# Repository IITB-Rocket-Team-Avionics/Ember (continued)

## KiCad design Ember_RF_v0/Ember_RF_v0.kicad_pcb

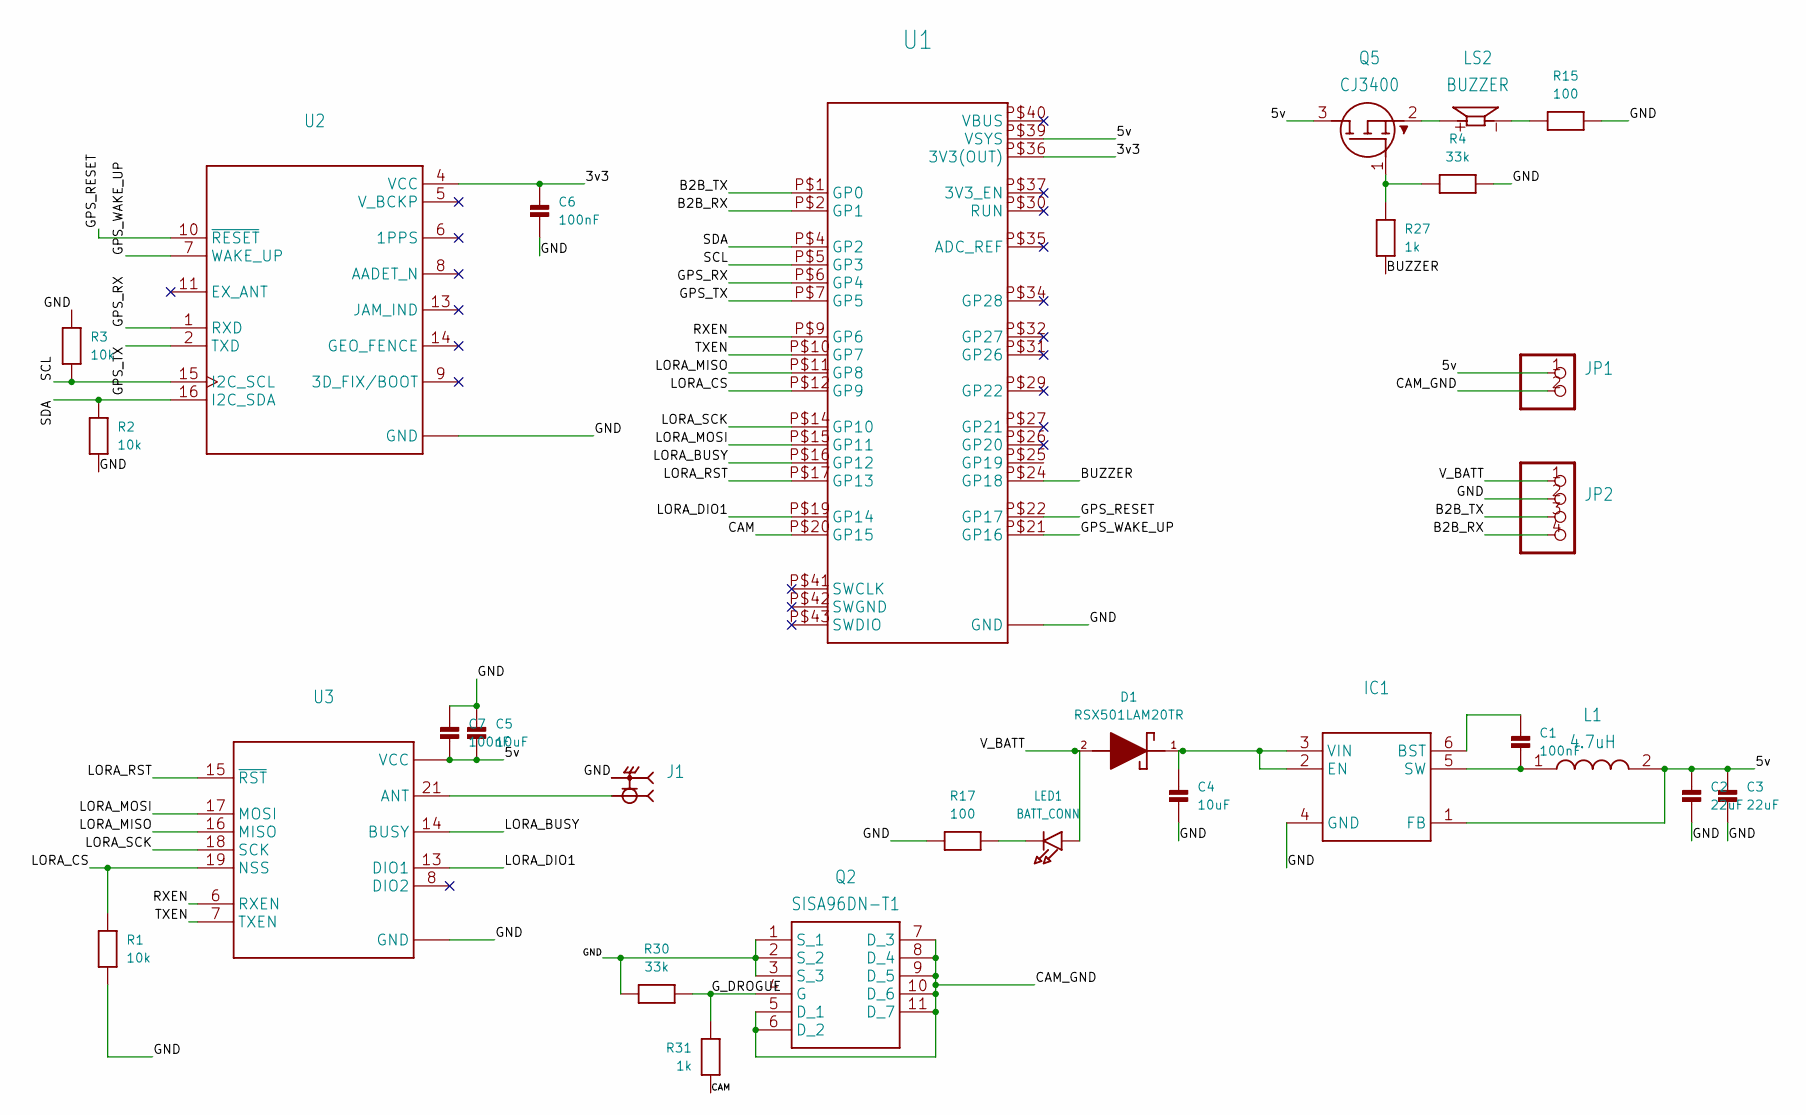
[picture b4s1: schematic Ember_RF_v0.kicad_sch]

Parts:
C1, C6, C7: 100nF; 0603
C2, C3: 22uF; 0603
C4, C5: 10uF; 0603
D1: RSX501LAM20TR; DIOM4725X105N; MOUSER_PART_NUMBER 755-RSX501LAM20TR; DigiKey_Part_Number RSX501LAM20CT-ND
IC1: SOT95P280X100-6N
J1: RFSOLUTIONS_CON-SMA-EDGE-S
JP1: 1X02_OVAL
JP2: 1X04_OVAL
L1: 4.7uH; INDPM3027X150N
LED1: BATT_CONN; CHIPLED_0603
LS2: BUZZER; CUI_CMT-8530S-SMT
Q2: SISA96DN-T1; SIS862DNT1GE3
Q5: CJ3400; SOT95P240X115-3N
R1, R2, R3: 10k; 0603
R4, R30: 33k; 0603
R15, R17: 100; 0603
R27, R31: 1k; 0603
U1: PICO-PKG-SMD
U2: XCVR_L89
U3: XCVR_E22-900M30S

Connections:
/3v3: C6.1, U1.P$36 (3V3(OUT)), U2.4 (VCC)
/5v: C2.1, C3.1, C5.2, C7.2, IC1.1 (FB), JP1.1, L1.2, Q5.3 (D), U1.P$39 (VSYS), U3.9 (VCC), U3.10 (VCC)
/B2B_RX: JP2.4, U1.P$2 (GP1)
/B2B_TX: JP2.3, U1.P$1 (GP0)
/BUZZER: R27.1, U1.P$24 (GP18)
/CAM: R31.1, U1.P$20 (GP15)
/CAM_GND: JP1.2, Q2.5 (D_1), Q2.6 (D_2), Q2.7 (D_3), Q2.8 (D_4), Q2.9 (D_5), Q2.10 (D_6), Q2.11 (D_7)
/GND: C2.2, C3.2, C4.2, C5.1, C6.2, C7.1, IC1.4 (GND), J1.G1 (2), J1.G2 (2), J1.G3 (2), J1.G4 (2), JP2.2, Q2.1 (S_1), Q2.2 (S_2), Q2.3 (S_3), R1.1, R2.1, R3.2, R4.2, R15.2, R17.1, R30.2, U1.P$3 (GND), U1.P$8 (GND), U1.P$13 (GND), U1.P$18 (GND), U1.P$23 (GND), U1.P$28 (GND), U1.P$33 (GND), U1.P$38 (GND), U2.3 (GND), U2.12 (GND), U3.1 (GND), U3.2 (GND), U3.3 (GND), U3.4 (GND), U3.5 (GND), U3.11 (GND), U3.12 (GND), U3.20 (GND), U3.22 (GND)
/GPS_RESET: U1.P$22 (GP17), U2.10 (~RESET)
/GPS_RX: U1.P$6 (GP4), U2.1 (RXD)
/GPS_TX: U1.P$7 (GP5), U2.2 (TXD)
/GPS_WAKE_UP: U1.P$21 (GP16), U2.7 (WAKE_UP)
/G_DROGUE: Q2.4 (G), R30.1, R31.2
/LORA_BUSY: U1.P$16 (GP12), U3.14 (BUSY)
/LORA_CS: R1.2, U1.P$12 (GP9), U3.19 (NSS)
/LORA_DIO1: U1.P$19 (GP14), U3.13 (DIO1)
/LORA_MISO: U1.P$11 (GP8), U3.16 (MISO)
/LORA_MOSI: U1.P$15 (GP11), U3.17 (MOSI)
/LORA_RST: U1.P$17 (GP13), U3.15 (~RST)
/LORA_SCK: U1.P$14 (GP10), U3.18 (SCK)
/RXEN: U1.P$9 (GP6), U3.6 (RXEN)
/SCL: R3.1, U1.P$5 (GP3), U2.15 (I2C_SCL)
/SDA: R2.2, U1.P$4 (GP2), U2.16 (I2C_SDA)
/TXEN: U1.P$10 (GP7), U3.7 (TXEN)
/V_BATT: D1.2, JP2.1, LED1.A
unnamed: C1.1, IC1.6 (BST)
unnamed: C1.2, IC1.5 (SW), L1.1
unnamed: C4.1, D1.1, IC1.2 (EN), IC1.3 (VIN)
unnamed: LED1.C, R17.2
unnamed: LS2.N, R15.1
unnamed: Q5.1 (G), R4.1, R27.2
unnamed: LS2.P, Q5.2 (S)
unnamed: J1.1, U3.21 (ANT)

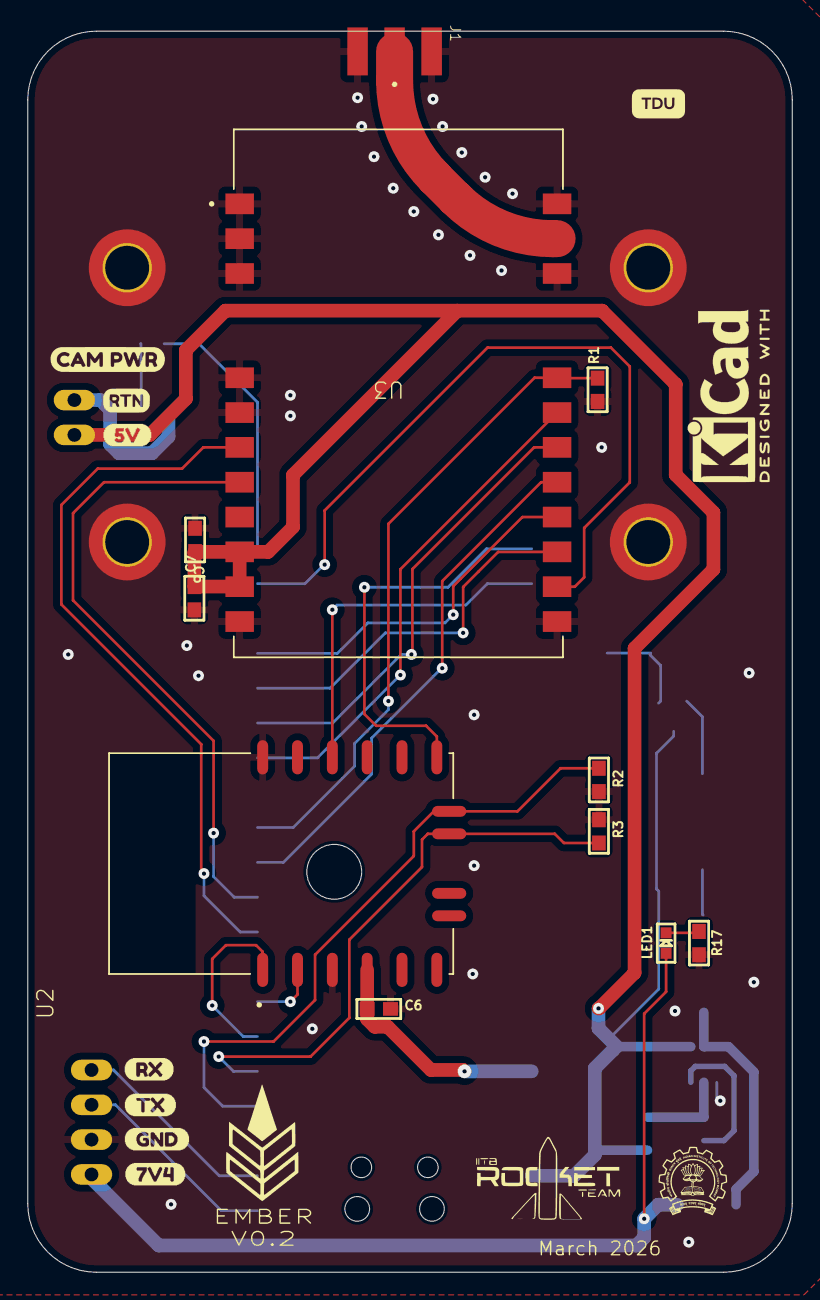
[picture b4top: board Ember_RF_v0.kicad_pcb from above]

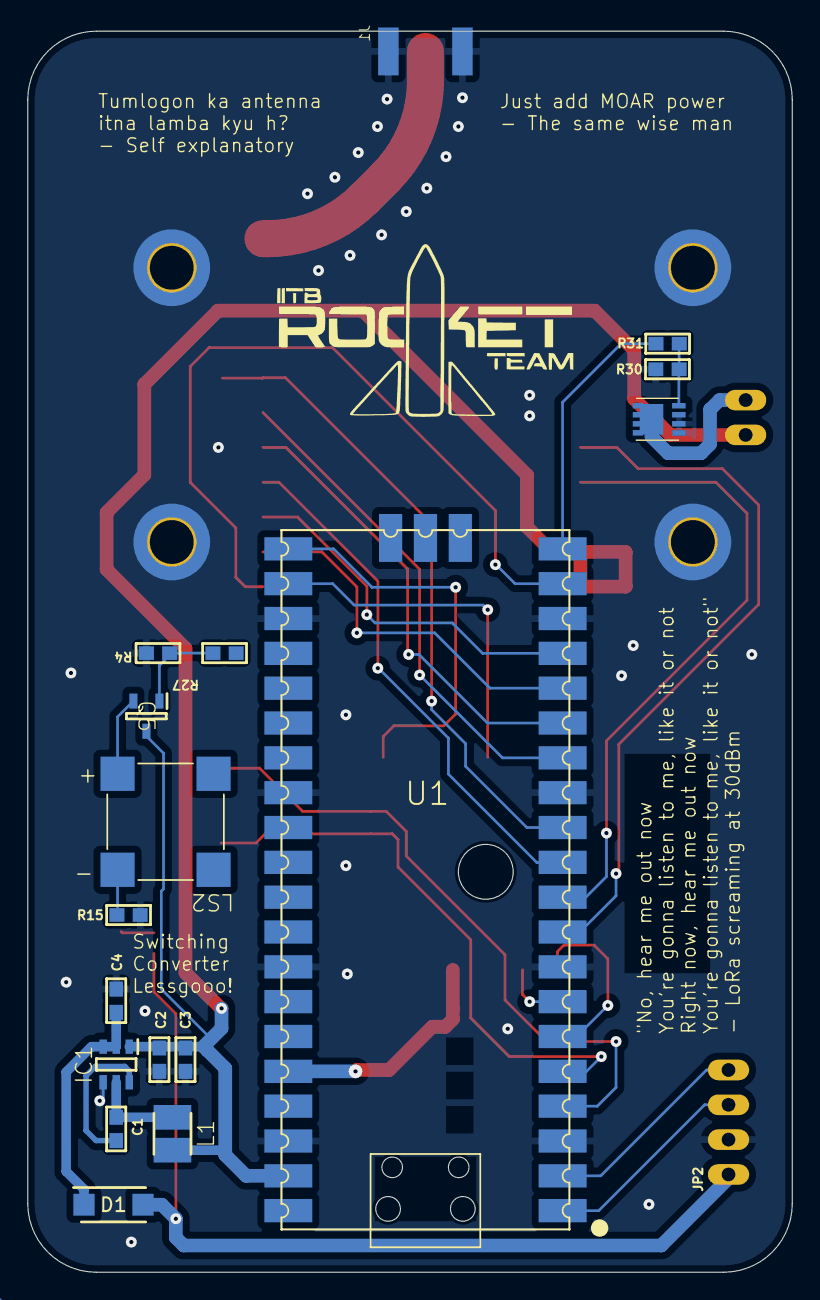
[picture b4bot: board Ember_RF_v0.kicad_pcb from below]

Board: 2 copper layers, 55.8 x 90.5 mm, 29 parts (18 on the bottom side), 33 nets.

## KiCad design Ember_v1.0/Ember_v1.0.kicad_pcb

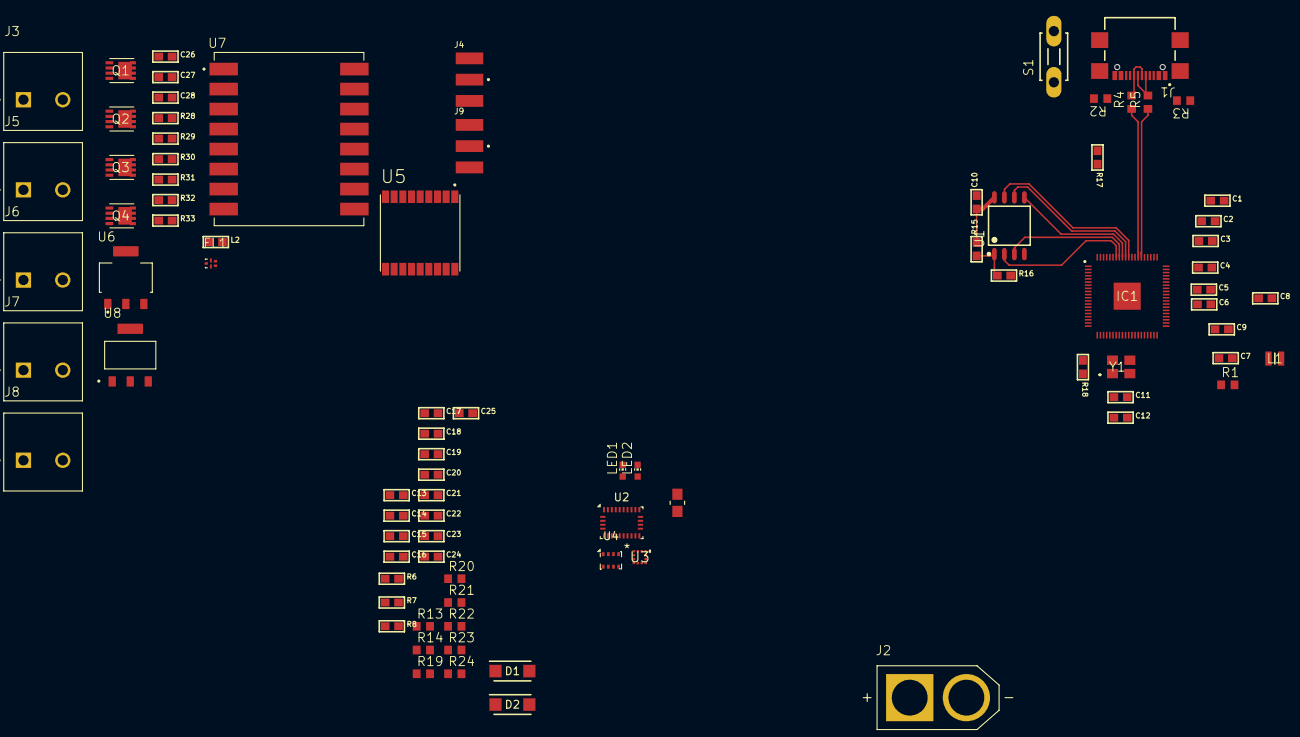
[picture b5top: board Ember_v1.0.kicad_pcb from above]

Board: 4 copper layers, 86 parts (0 on the bottom side), 55 nets.

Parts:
C1, C2, C3, C4, C6, C10, C13, C16: 100 nF; 0603
C5: 1 uF; 0603
C7, C8, C9: 4.7 uF; 0603
C11, C12: 18pF; 0603
C14, C15, C21: 10 uF; 0603
C17, C18, C19, C26, C27, C28: 0603
C20, C22, C23: 120 pF; 0603
C24, C25: 20 pF; 0603
D1, D2: RSX501LAM20TR; DIOM4725X105N
FL1: Saw_filter; FIL_AFS14A04-1575.42-T3
IC1: QFN40P1000X1000X90-81N
J1: USB_C; GCT_USB4110GFA
J2: BATT_CONN; AMASS_XT60-M
J3: DROGUE; ONSHORE_OSTTA020161
J4, J9: RFSOLUTIONS_CON-SMA-EDGE-S
J5: MAIN; ONSHORE_OSTTA020161
J6: MAN2; ONSHORE_OSTTA020161
J7: DROGUE2; ONSHORE_OSTTA020161
J8: ARM; ONSHORE_OSTTA020161
L1: 3.3 uH; LQM2MPN1R0NG0L
L2: 0603
LED1: V_BATT; CHIP-LED0603
LED2: VBUS; CHIP-LED0603
Q1, Q2, Q3, Q4: SISA96DN-T1; SIS862DNT1GE3
R1: R0603
R2, R3: 5.1k; R0603
R4, R5: 27.4; R0603
R6, R28, R30, R32: 33k; 0603
R7, R18, R29, R31, R33: 1k; 0603
R8: 4.7k; 0603
R13, R14: 100; R0603
R15: 10 kohm; 0603
R16: 0 ohm; 0603
R17: 0603
R19, R20, R21, R22, R23, R24: 10 kohm; R0603
S1: DTS-3
U1: FLASH_128K; SOIC127P790X216-8N
U2: BNO055; LGA-28_5.2x3.8mm_P0.5mm
U3: LGA12_2X2X0P9_ROM
U4: BMP280; Bosch_LGA-8_2x2.5mm_P0.65mm_ClockwisePinNumbering
U5: Teseo_liv3f; TESEO-LIV3F
U6, U8: SOT229P700X180-4N
U7: Waveshare_SX1262; XCVR_CORE1262-868M
XTAL1: XTAL_FC135; XTAL_FC-135_EPS
Y1: YSX321SL

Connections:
/Main_board/1v1: C5.1, C6.1, C8.1, IC1.10 (DVDD_1), IC1.32 (DVDD_2), IC1.51 (DVDD_3), IC1.65 (VREG_FB), L1.2
/Main_board/3v3: C1.1, C2.1, C3.1, C4.1, C9.1, C10.1, C13.2, C14.1, C15.1, C17.1, C18.1, IC1.5 (IOVDD_1), IC1.15 (IOVDD_2), IC1.24 (IOVDD_3), IC1.29 (IOVDD_4), IC1.35 (RUN), IC1.41 (IOVDD_5), IC1.50 (IOVDD_6), IC1.59 (ADC_AVDD), IC1.60 (IOVDD_7), IC1.64 (VREG_VIN), IC1.68 (USB_OTP_VDD), IC1.69 (QSPI_IOVDD), IC1.76 (IOVDD_8), R1.2, R15.2, R20.1, R21.1, R22.1, R24.1, U1.8 (VCC), U2.3 (VDD), U2.4 (~BOOT_LOAD_PIN), U2.28 (VDDIO), U3.1 (SDO/ADDR), U3.3 (IO_VDD), U3.7 (VDD), U3.10 (NCS), U4.6 (VDDIO), U4.8 (VDD), U6.2 (VOUT), U6.4 (VOUT)
/Main_board/5v: C26.1, C27.1, D1.2, LED1.A, U8.2 (VOUT)
/Main_board/D_N: IC1.66 (USB_DM), R5.1
/Main_board/D_Nr: J1.A7 (DN1), J1.B7 (DN2), R5.2
/Main_board/D_P: IC1.67 (USB_DP), R4.1
/Main_board/D_Pr: J1.A6 (DP1), J1.B6 (DP2), R4.2
/Main_board/FLASH_EXT_CS: IC1.77 (GPIO0), R16.2
/Main_board/GND: C1.2, C2.2, C3.2, C4.2, C5.2, C6.2, C7.2, C8.2, C9.2, C10.2, C11.2, C12.1, C13.1, C14.2, C15.2, C16.1, C17.2, C18.2, C19.2, C24.1, C25.1, C26.2, C27.2, C28.2, IC1.62 (VREG_PGND), IC1.81 (GND), J1.A1/B12 (GND), J1.B1/A12 (GND), J1.S1 (GND), J1.S2 (GND), J1.S3 (GND), J1.S4 (GND), J2.N (NEG), Q1.1 (S_1), Q1.2 (S_2), Q1.3 (S_3), Q2.1 (S_1), Q2.2 (S_2), Q2.3 (S_3), Q3.1 (S_1), Q3.2 (S_2), Q3.3 (S_3), Q4.1 (S_1), Q4.2 (S_2), Q4.3 (S_3), R2.2, R3.1, R6.2, R14.2, R19.1, R23.1, R28.2, R30.2, R32.2, S1.2, U1.4 (GND), U2.2 (GND), U2.5 (PS1), U2.6 (PS0), U2.18 (COM2), U2.25 (GNDIO), U3.4 (TRIG), U3.8 (GND_2), U3.9 (GND), U4.1 (GND), U4.7 (GND), U6.1 (ADJ/GND), U8.1 (GND/ADJ), Y1.2 (GND_1), Y1.4 (GND_2)
/Main_board/G_DROGUE: Q2.4 (G), R30.1, R31.2
/Main_board/G_MAIN: Q3.4 (G), R32.1, R33.2
/Main_board/G_MAIN2: Q1.4 (G), R28.1, R29.2
/Main_board/PYRO_DROGUE: J3.2, Q2.5 (D_1), Q2.6 (D_2), Q2.7 (D_3), Q2.8 (D_4), Q2.9 (D_5), Q2.10 (D_6), Q2.11 (D_7)
/Main_board/PYRO_DROGUE2: J7.2, Q4.5 (D_1), Q4.6 (D_2), Q4.7 (D_3), Q4.8 (D_4), Q4.9 (D_5), Q4.10 (D_6), Q4.11 (D_7)
/Main_board/PYRO_MAIN: J5.2, Q3.5 (D_1), Q3.6 (D_2), Q3.7 (D_3), Q3.8 (D_4), Q3.9 (D_5), Q3.10 (D_6), Q3.11 (D_7)
/Main_board/PYRO_MAIN2: J6.2, Q1.5 (D_1), Q1.6 (D_2), Q1.7 (D_3), Q1.8 (D_4), Q1.9 (D_5), Q1.10 (D_6), Q1.11 (D_7)
/Main_board/QSPI_SCLK: IC1.71 (QSPI_SCLK), U1.6 (CLK)
/Main_board/QSPI_SD0: IC1.72 (QSPI_SD0), U1.5 (DI(IO0))
/Main_board/QSPI_SD1: IC1.74 (QSPI_SD1), U1.2 (DO(IO1))
/Main_board/QSPI_SD2: IC1.73 (QSPI_SD2), U1.3 (~WP(IO2))
/Main_board/QSPI_SD3: IC1.70 (QSPI_SD3), U1.7 (~HOLD/~RESET(IO3))
/Main_board/QSPI_SS: IC1.75 (QSPI_SS), R17.2
/Main_board/SCL: IC1.2 (GPIO5), R21.2, U2.19 (COM1), U3.12 (SCLK/SCL), U4.4 (SCK)
/Main_board/SDA: IC1.1 (GPIO4), R20.2, U2.20 (COM0), U3.2 (SDI/SDA), U4.3 (SDI)
/Main_board/VBUS: D2.2, J1.A4/B9 (VBUS), J1.B4/A9 (VBUS), LED2.A
/Main_board/VCC_PYRO: J3.1, J5.1, J6.1, J7.1, J8.1
/Main_board/V_BATT: C28.1, J2.P (POS), J8.2, U8.3 (VIN)
/Main_board/V_MUX_OUT: C19.1, D1.1, D2.1, U6.3 (VIN)
/Main_board/XIN: C12.2, IC1.30 (XIN), Y1.3 (CRYSTAL_2)
/Main_board/XIN32: C24.2, U2.27 (XIN32), XTAL1.1
/Main_board/XOUT: IC1.31 (XOUT), R18.1
/Main_board/XOUT32: C25.2, U2.26 (XOUT32), XTAL1.2
/RF_board/3v3: C21.2, U5.6 (VBATT), U5.7 (VCC_IO), U5.8 (VCC), U7.8 (3V3)
/RF_board/GND: C21.1, C23.1, FL1.B (GND), FL1.D (GND), FL1.E (GND), J4.G1 (2), J4.G2 (2), J4.G3 (2), J4.G4 (2), J9.G1 (2), J9.G2 (2), J9.G3 (2), J9.G4 (2), R8.1, U5.1 (GND), U5.10 (GND_RF), U5.12 (GND_RF), U7.1 (GND), U7.2 (GND), U7.7 (GND), U7.15 (GND)
/RF_board/GPS_ANT: C22.1, C23.2, J4.1, L2.2
/RF_board/GPS_RF_IN: C20.2, U5.11 (RF_IN)
/RF_board/LORA_CS: R8.2, U7.14 (CS)
/RF_board/LoRa_ANT: J9.1, U7.16 (ANT)
/RF_board/SAW_IN: C22.2, FL1.C (IN)
/RF_board/SAW_OUT: C20.1, FL1.A (OUT)
unnamed: C7.1, IC1.61 (VREG_AVDD), R1.1
unnamed: C11.1, R18.2, Y1.1 (CRYSTAL_1)
unnamed: C16.2, U2.9 (CAP)
unnamed: IC1.63 (VREG_LX), L1.1
unnamed: J1.A5 (CC1), R3.2
unnamed: J1.B5 (CC2), R2.1
unnamed: LED1.C, R14.1
unnamed: LED2.C, R13.1
unnamed: Q4.4 (G), R6.1, R7.2
unnamed: R17.1, S1.1
unnamed: R15.1, R16.1, U1.1 (~CS)
unnamed: R23.2, U2.17 (COM3)
unnamed: R22.2, U2.11 (~RESET)
unnamed: R24.2, U4.2 (CSB)
unnamed: R19.2, U4.5 (SDO)

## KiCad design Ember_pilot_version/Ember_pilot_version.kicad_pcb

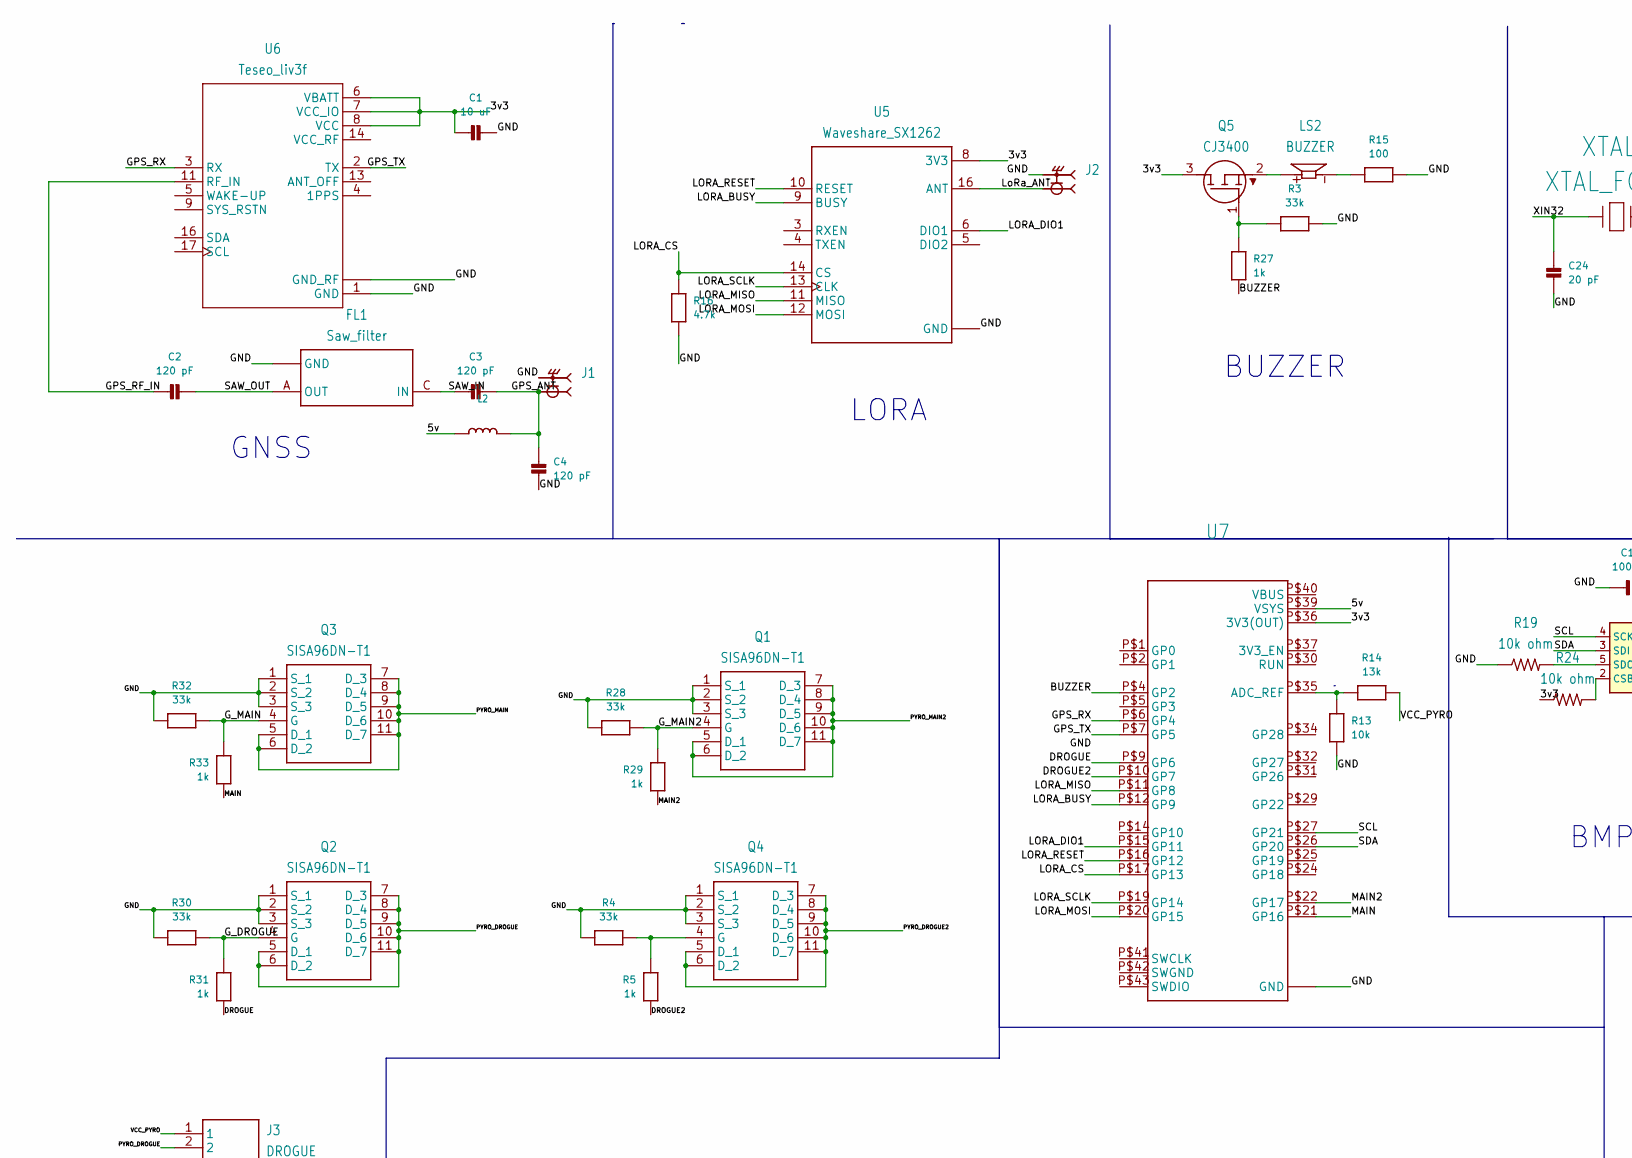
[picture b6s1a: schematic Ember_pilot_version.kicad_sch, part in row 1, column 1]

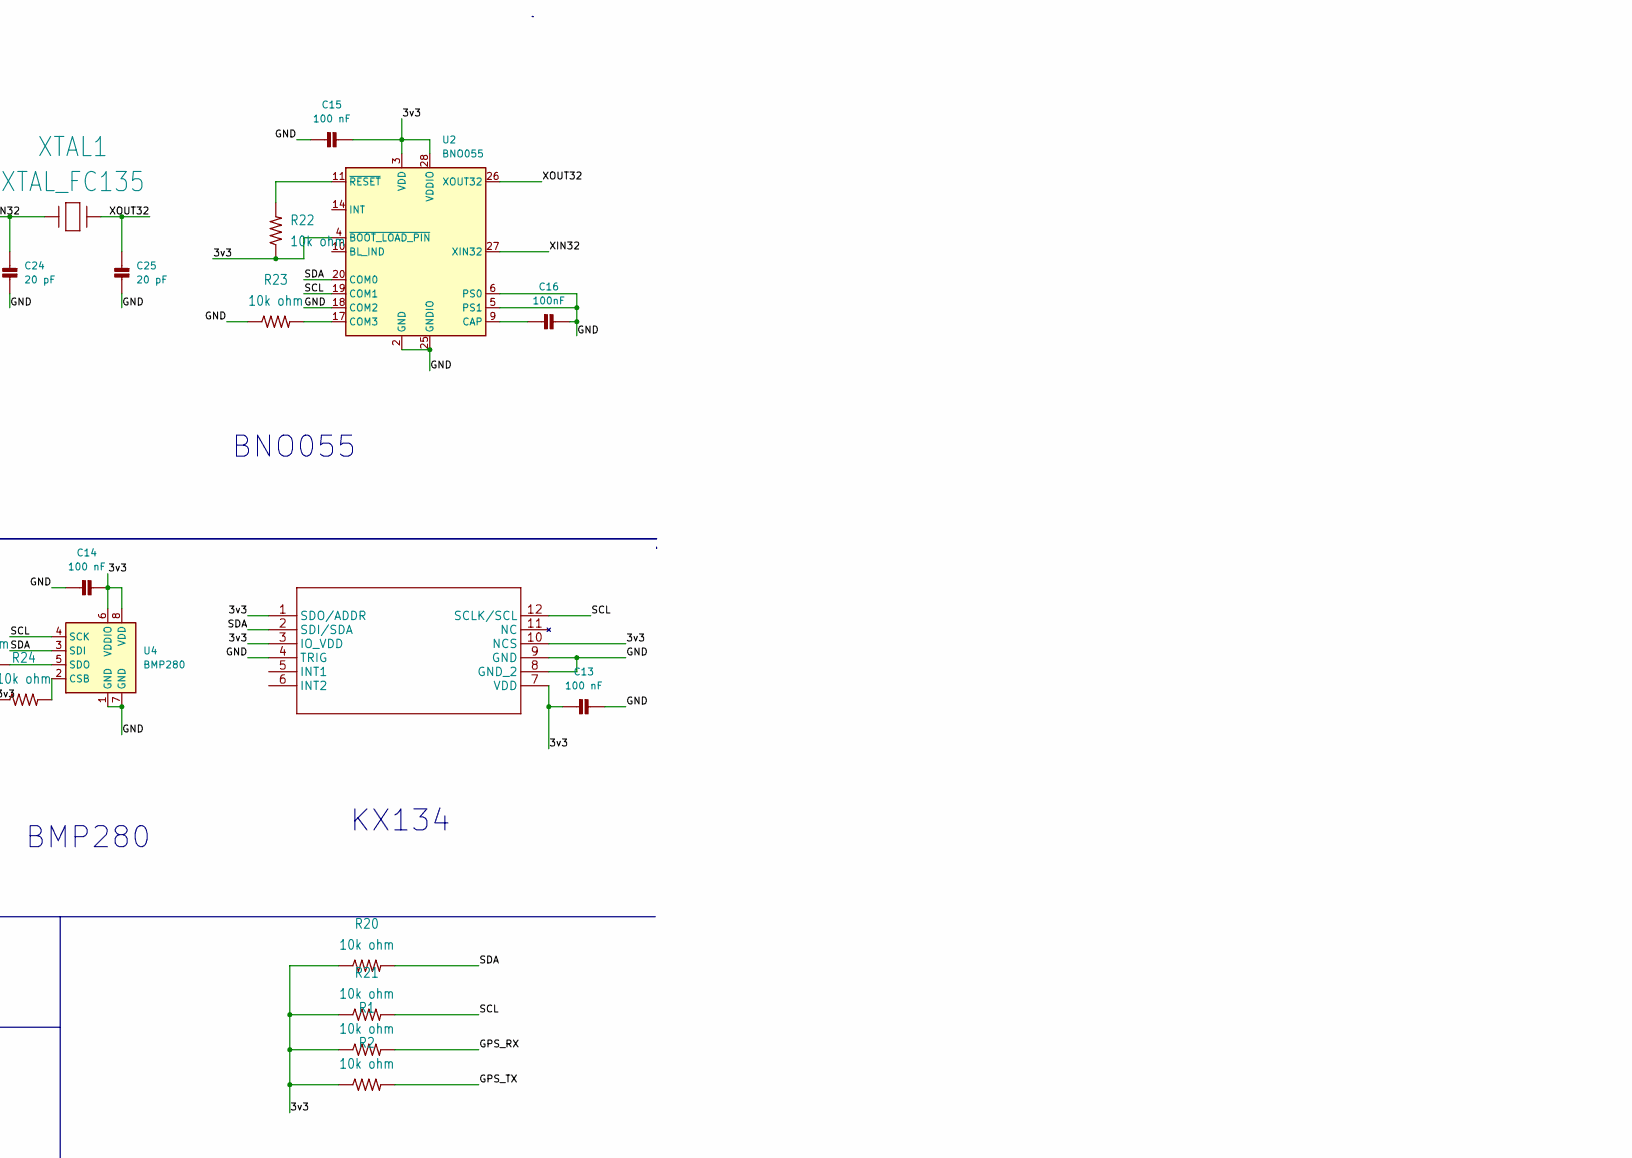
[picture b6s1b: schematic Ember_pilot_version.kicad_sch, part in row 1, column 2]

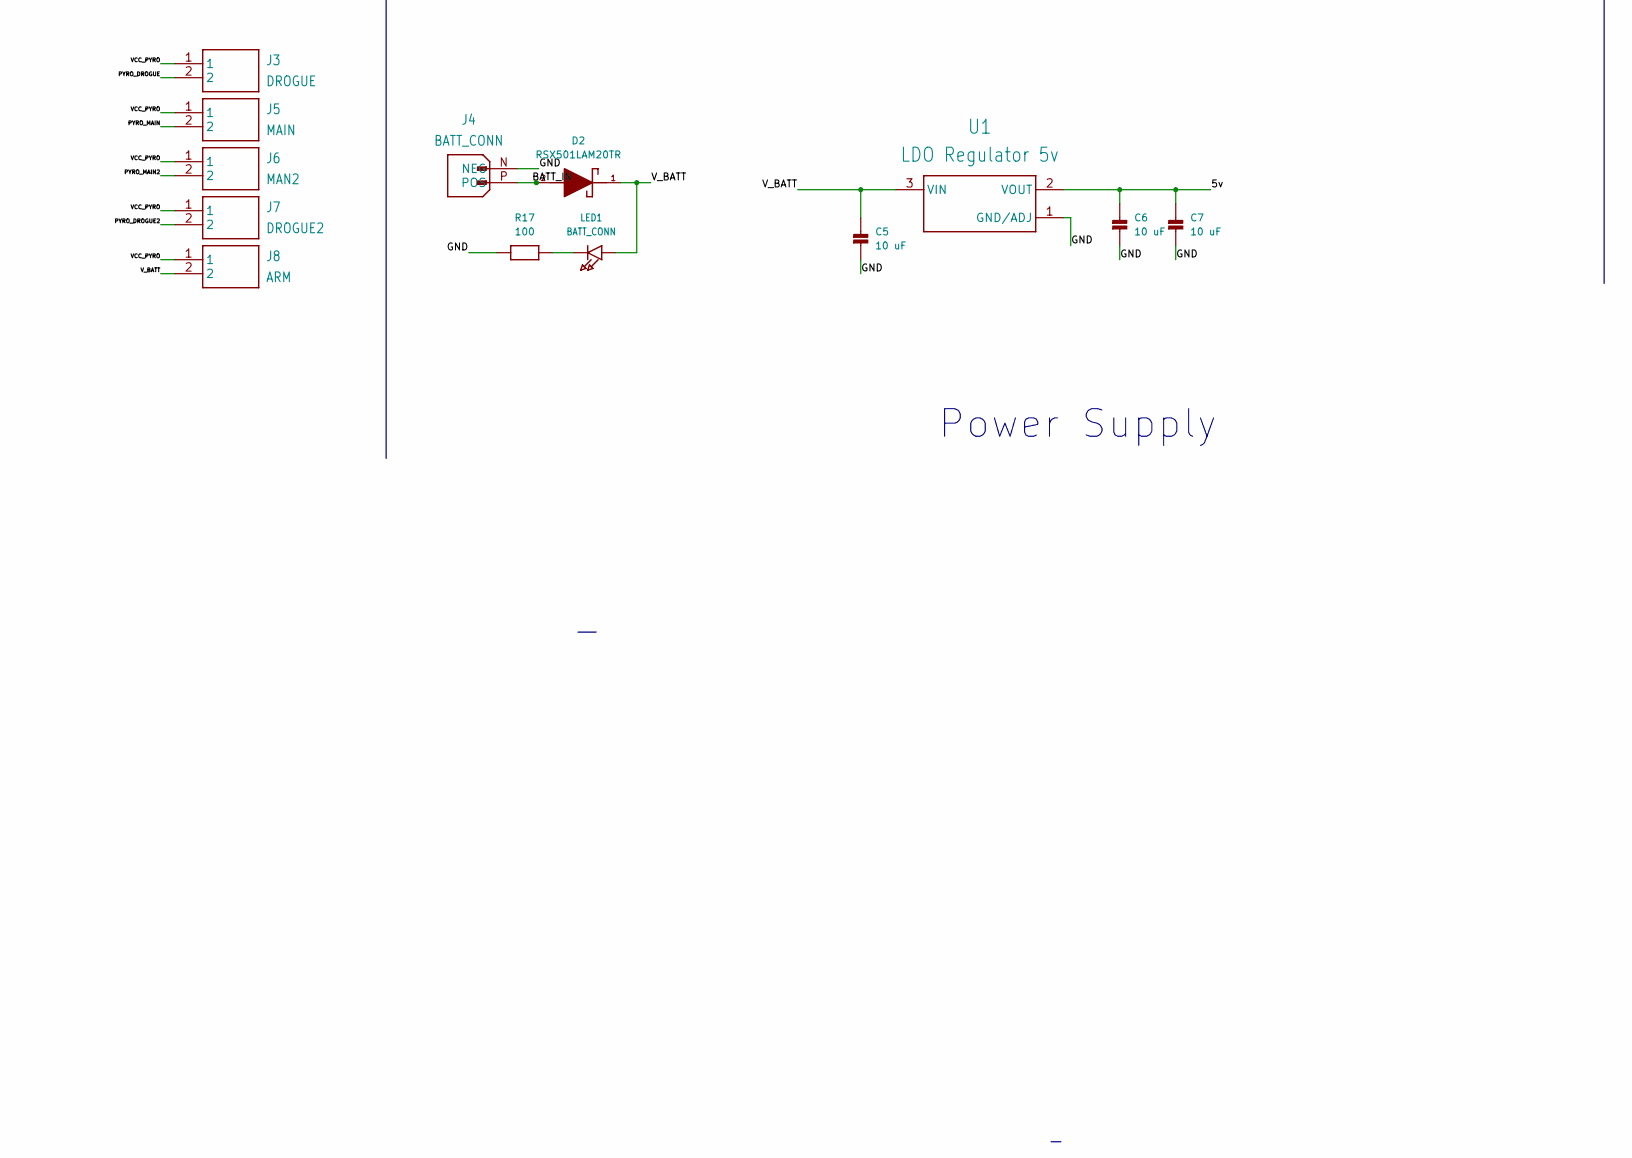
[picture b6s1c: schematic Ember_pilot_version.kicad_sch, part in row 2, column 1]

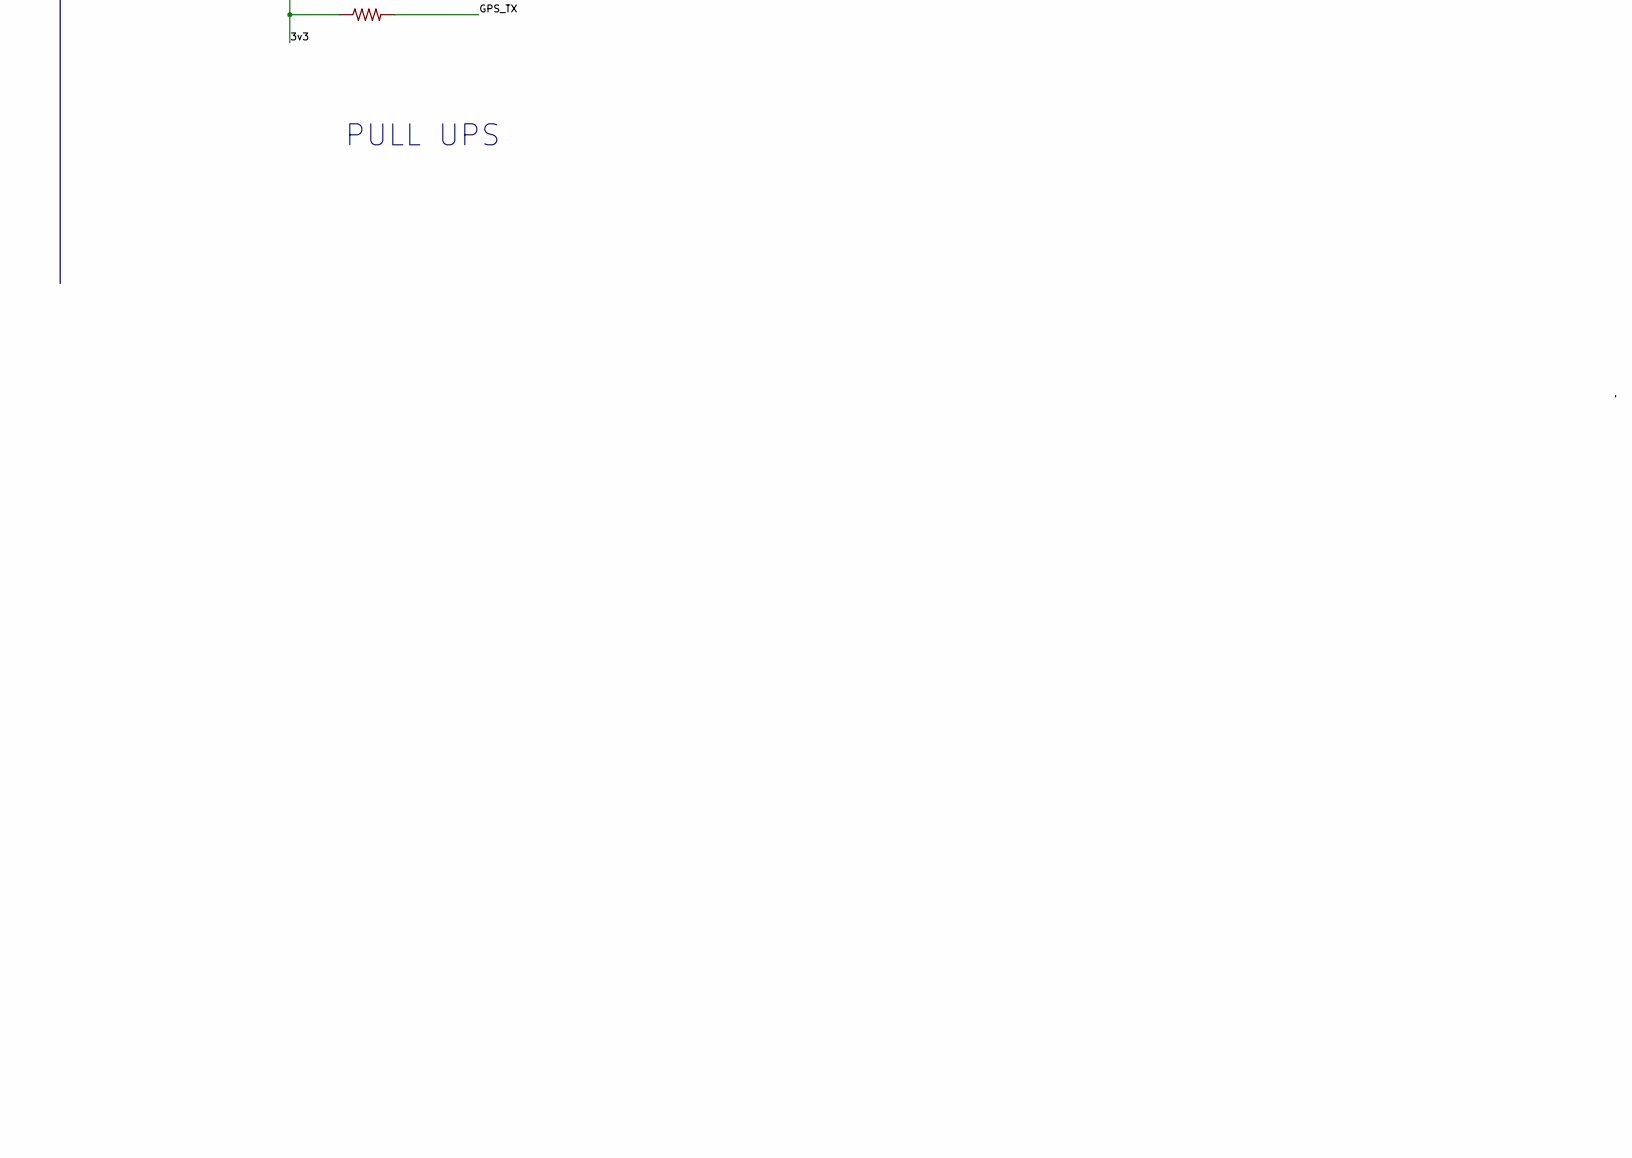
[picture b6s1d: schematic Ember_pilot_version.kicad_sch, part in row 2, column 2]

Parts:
C1, C5, C6, C7: 10 uF; 0603
C2, C3, C4: 120 pF; 0603
C13, C14, C15: 100 nF; 0603
C16: 100nF; 0603
C24, C25: 20 pF; 0603
D2: RSX501LAM20TR; DIOM4725X105N; MOUSER_PART_NUMBER 755-RSX501LAM20TR; DigiKey_Part_Number RSX501LAM20CT-ND
FL1: Saw_filter; FIL_AFS14A04-1575.42-T3
J1, J2: RFSOLUTIONS_CON-SMA-EDGE-S
J3: DROGUE; ONSHORE_OSTTA020161
J4: BATT_CONN; AMASS_XT60-M
J5: MAIN; ONSHORE_OSTTA020161
J6: MAN2; ONSHORE_OSTTA020161
J7: DROGUE2; ONSHORE_OSTTA020161
J8: ARM; ONSHORE_OSTTA020161
L2: 0603
LED1: BATT_CONN; CHIPLED_0603
LS2: BUZZER; CUI_CMT-8530S-SMT
Q1, Q2, Q3, Q4: SISA96DN-T1; SIS862DNT1GE3
Q5: CJ3400; SOT95P240X115-3N
R1, R2, R19, R20, R21, R22, R23, R24: 10k ohm; R0603
R3, R4, R28, R30, R32: 33k; 0603
R5, R27, R29, R31, R33: 1k; 0603
R13: 10k; 0603
R14: 13k; 0603
R15, R17: 100; 0603
R16: 4.7k; 0603
U1: LDO Regulator 5v; SOT229P700X180-4N
U2: BNO055; LGA-28_5.2x3.8mm_P0.5mm
U3: LGA12_2X2X0P9_ROM
U4: BMP280; Bosch_LGA-8_2x2.5mm_P0.65mm_ClockwisePinNumbering
U5: Waveshare_SX1262; XCVR_CORE1262-868M
U6: Teseo_liv3f; TESEO-LIV3F
U7: PICO-PKG-SMD
XTAL1: XTAL_FC135; XTAL_FC-135_EPS

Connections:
/3v3: C1.2, C13.2, C14.1, C15.1, Q5.3 (D), R1.1, R2.1, R20.1, R21.1, R22.1, R24.1, U2.3 (VDD), U2.4 (~BOOT_LOAD_PIN), U2.28 (VDDIO), U3.1 (SDO/ADDR), U3.3 (IO_VDD), U3.7 (VDD), U3.10 (NCS), U4.6 (VDDIO), U4.8 (VDD), U5.8 (3V3), U6.6 (VBATT), U6.7 (VCC_IO), U6.8 (VCC), U7.P$36 (3V3(OUT))
/5v: C6.1, C7.1, L2.1, U1.2 (VOUT), U7.P$39 (VSYS)
/BATT_IN: D2.2, J4.P (POS)
/BUZZER: R27.1, U7.P$4 (GP2)
/DROGUE: R31.1, U7.P$9 (GP6)
/DROGUE2: R5.1, U7.P$10 (GP7)
/GND: C1.1, C4.1, C5.2, C6.2, C7.2, C13.1, C14.2, C15.2, C16.1, C24.1, C25.1, FL1.B (GND), FL1.D (GND), FL1.E (GND), J1.G1 (2), J1.G2 (2), J1.G3 (2), J1.G4 (2), J2.G1 (2), J2.G2 (2), J2.G3 (2), J2.G4 (2), J4.N (NEG), Q1.1 (S_1), Q1.2 (S_2), Q1.3 (S_3), Q2.1 (S_1), Q2.2 (S_2), Q2.3 (S_3), Q3.1 (S_1), Q3.2 (S_2), Q3.3 (S_3), Q4.1 (S_1), Q4.2 (S_2), Q4.3 (S_3), R3.2, R4.2, R13.1, R15.2, R16.1, R17.1, R19.1, R23.1, R28.2, R30.2, R32.2, U1.1 (GND/ADJ), U2.2 (GND), U2.5 (PS1), U2.6 (PS0), U2.18 (COM2), U2.25 (GNDIO), U3.4 (TRIG), U3.8 (GND_2), U3.9 (GND), U4.1 (GND), U4.7 (GND), U5.1 (GND), U5.2 (GND), U5.7 (GND), U5.15 (GND), U6.1 (GND), U6.10 (GND_RF), U6.12 (GND_RF), U7.P$3 (GND), U7.P$8 (GND), U7.P$13 (GND), U7.P$18 (GND), U7.P$23 (GND), U7.P$28 (GND), U7.P$33 (GND), U7.P$38 (GND)
/GPS_ANT: C3.1, C4.2, J1.1, L2.2
/GPS_RF_IN: C2.2, U6.11 (RF_IN)
/GPS_RX: R1.2, U6.3 (RX), U7.P$6 (GP4)
/GPS_TX: R2.2, U6.2 (TX), U7.P$7 (GP5)
/G_DROGUE: Q2.4 (G), R30.1, R31.2
/G_MAIN: Q3.4 (G), R32.1, R33.2
/G_MAIN2: Q1.4 (G), R28.1, R29.2
/LORA_BUSY: U5.9 (BUSY), U7.P$12 (GP9)
/LORA_CS: R16.2, U5.14 (CS), U7.P$17 (GP13)
/LORA_DIO1: U5.6 (DIO1), U7.P$15 (GP11)
/LORA_MISO: U5.11 (MISO), U7.P$11 (GP8)
/LORA_MOSI: U5.12 (MOSI), U7.P$20 (GP15)
/LORA_RESET: U5.10 (RESET), U7.P$16 (GP12)
/LORA_SCLK: U5.13 (CLK), U7.P$19 (GP14)
/LoRa_ANT: J2.1, U5.16 (ANT)
/MAIN: R33.1, U7.P$21 (GP16)
/MAIN2: R29.1, U7.P$22 (GP17)
/PYRO_DROGUE: J3.2, Q2.5 (D_1), Q2.6 (D_2), Q2.7 (D_3), Q2.8 (D_4), Q2.9 (D_5), Q2.10 (D_6), Q2.11 (D_7)
/PYRO_DROGUE2: J7.2, Q4.5 (D_1), Q4.6 (D_2), Q4.7 (D_3), Q4.8 (D_4), Q4.9 (D_5), Q4.10 (D_6), Q4.11 (D_7)
/PYRO_MAIN: J5.2, Q3.5 (D_1), Q3.6 (D_2), Q3.7 (D_3), Q3.8 (D_4), Q3.9 (D_5), Q3.10 (D_6), Q3.11 (D_7)
/PYRO_MAIN2: J6.2, Q1.5 (D_1), Q1.6 (D_2), Q1.7 (D_3), Q1.8 (D_4), Q1.9 (D_5), Q1.10 (D_6), Q1.11 (D_7)
/SAW_IN: C3.2, FL1.C (IN)
/SAW_OUT: C2.1, FL1.A (OUT)
/SCL: R21.2, U2.19 (COM1), U3.12 (SCLK/SCL), U4.4 (SCK), U7.P$27 (GP21)
/SDA: R20.2, U2.20 (COM0), U3.2 (SDI/SDA), U4.3 (SDI), U7.P$26 (GP20)
/VCC_PYRO: J3.1, J5.1, J6.1, J7.1, J8.1, R14.2
/V_BATT: C5.1, D2.1, J8.2, LED1.A, U1.3 (VIN)
/XIN32: C24.2, U2.27 (XIN32), XTAL1.1
/XOUT32: C25.2, U2.26 (XOUT32), XTAL1.2
unnamed: C16.2, U2.9 (CAP)
unnamed: LED1.C, R17.2
unnamed: LS2.N, R15.1
unnamed: Q4.4 (G), R4.1, R5.2
unnamed: Q5.1 (G), R3.1, R27.2
unnamed: LS2.P, Q5.2 (S)
unnamed: R23.2, U2.17 (COM3)
unnamed: R22.2, U2.11 (~RESET)
unnamed: R24.2, U4.2 (CSB)
unnamed: R19.2, U4.5 (SDO)
unnamed: R13.2, R14.1, U7.P$35 (ADC_REF)

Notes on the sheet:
KX134
GNSS
BUZZER
BNO055
PULL UPS
LORA
BMP280
Power Supply
